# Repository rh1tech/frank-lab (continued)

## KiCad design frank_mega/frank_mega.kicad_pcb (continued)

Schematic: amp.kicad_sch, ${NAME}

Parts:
C36, C41, C46: 1u; C_0805_2012Metric
C37, C38, C39, C43, C44: 10u; C_0805_2012Metric
C40, C45: 100n; C_0805_2012Metric
C42: 10u; CP_Radial_D4.0mm_P1.50mm
C47: 100u; C_Radial_D6.3mm_P2.50mm
R101, R102, R103, R104, R105, R106, R107, R108, R109, R112, R116: 10K; R_0805_2012Metric
R110, R111: 47K; R_0805_2012Metric
R113: 100R; R_0805_2012Metric
R114, R115: 20K; R_0805_2012Metric
U19: PAM8403D; SOP-16_P1.27mm; Mouser Part Number 700-MAX232CSE
U20: LM358; SO-8

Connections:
/Audio Multiplexer/AMP_IN_L: C37.1, R102.1; also elsewhere on the board
/Audio Multiplexer/AMP_IN_R: C38.1, R104.1; also elsewhere on the board
/Audio/AMP_OUTL: C43.2, R114.2; also elsewhere on the board
/Audio/AMP_OUTR: C44.2, R115.2; also elsewhere on the board
/Audio/AMP_PAM_OUTL_M: U19.3 (-OUTL); also elsewhere on the board
/Audio/AMP_PAM_OUTL_P: U19.1 (+OUT_L); also elsewhere on the board
/Audio/AMP_PAM_OUTR_M: U19.14 (-OUT_R); also elsewhere on the board
/Audio/AMP_PAM_OUTR_P: U19.16 (+OUT_R); also elsewhere on the board
/MONO_L: C36.1, R101.1, R102.2; also elsewhere on the board
/MONO_R: C41.1, R103.1, R104.2; also elsewhere on the board
/SHND: R116.2, U19.12 (SHND); also elsewhere on the board
GND: C39.1, C40.2, C42.2, C45.1, C46.2, C47.2, R101.2, R103.2, R106.1, R114.1, R115.1, U19.2 (PGND), U19.11 (GND), U19.15 (PGND), U20.4 (V-); also elsewhere on the board
unnamed: C36.2, R107.2
unnamed: C37.2, R108.2
unnamed: C38.2, R109.2
unnamed: C41.2, R112.2
unnamed: C43.1, R110.1, U20.7
unnamed: C44.1, R111.1, U20.1
unnamed: R107.1, U19.7 (INL)
unnamed: R112.1, U19.10 (INR)
unnamed: C40.1, U19.8 (VREF)
unnamed: C39.2, R105.1, R106.2, U20.3 (+), U20.5 (+)
unnamed: R109.1, R111.2, U20.2 (-)
unnamed: R108.1, R110.2, U20.6 (-)
unnamed: C42.1, C45.2, R105.2, R113.2, U20.8 (V+)
VBUS: C46.1, C47.1, R113.1, R116.1, U19.4 (PVDD), U19.5 (MUTE), U19.6 (VDD), U19.13 (PVDD); also elsewhere on the board

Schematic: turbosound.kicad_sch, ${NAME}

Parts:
C15, C16: 22p; C_0805_2012Metric
C17, C19: 100u; C_Radial_D6.3mm_P2.50mm
C18, C20, C21, C22: 100n; C_0805_2012Metric
D2, D3: 1N4148; D_SOD-323
LD2, LD3: Orange; LED_0805
Q1: BC850; SOT-23
R21, R23, R28, R36, R37: 1K; R_0805_2012Metric
R22: 100K; R_0805_2012Metric
R24, R25, R38, R39: 4.7K; R_0805_2012Metric
R26, R27, R40, R41: 2K; R_0805_2012Metric
R29, R30, R31, R32, R33, R34, R35, R44, R46, R49, R51, R53, R56, R58: 10K; R_0805_2012Metric
R42, R43, R45, R48, R50, R52, R54, R57, R59: 20K; R_0805_2012Metric
R47, R55: 120R; R_0805_2012Metric
S8: TS Reset; Button_SMD_3x4x2mm; Mouser Part Number 611-KMR221G-LFS
U5, U7: JFC95101; DIP-40_W15.24mm_Socket
U6: 74HC74; SOIC-14_P1.27mm
U8, U9: 74HC595; SOP-16_P1.27mm
X1: 3.58 MHz; Crystal_HC49-S

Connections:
/Audio/TS/A1: R26.2, U5.4 (B)
/Audio/TS/A2: R40.2, U7.4 (B)
/Audio/TS/B1: R24.2, R25.2, U5.3 (A)
/Audio/TS/B2: R38.2, R39.2, U7.3 (A)
/Audio/TS/BEEP: R32.2, R33.2, U9.4 (QE)
/Audio/TS/C1: R27.2, U5.38 (C)
/Audio/TS/C2: R41.2, U7.38 (C)
/Audio/TS/CLK_1.75M: U5.22 (CLOCK), U6.5 (Q), U7.22 (CLOCK)
/Audio/TS/COVOX_OUT: R30.2, R31.2, R58.2, R59.1
/Audio/TS/DA0: U5.37 (DA0), U7.37 (DA0), U8.15 (QA)
/Audio/TS/DA1: U5.36 (DA1), U7.36 (DA1), U8.1 (QB)
/Audio/TS/DA2: U5.35 (DA2), U7.35 (DA2), U8.2 (QC)
/Audio/TS/DA3: U5.34 (DA3), U7.34 (DA3), U8.3 (QD)
/Audio/TS/DA4: U5.33 (DA4), U7.33 (DA4), U8.4 (QE)
/Audio/TS/DA5: U5.32 (DA5), U7.32 (DA5), U8.5 (QF)
/Audio/TS/DA6: U5.31 (DA6), U7.31 (DA6), U8.6 (QG)
/Audio/TS/DA7: U5.30 (DA7), U7.30 (DA7), U8.7 (QH)
/Audio/TS/DAC0: R43.2, U7.13 (IOB0)
/Audio/TS/DAC1: R45.2, U7.12 (IOB1)
/Audio/TS/DAC2: R48.2, U7.11 (IOB2)
/Audio/TS/DAC3: R50.2, U7.10 (IOB3)
/Audio/TS/DAC4: R52.2, U7.9 (IOB4)
/Audio/TS/DAC5: R54.2, U7.8 (IOB5)
/Audio/TS/DAC6: R57.2, U7.7 (IOB6)
/Audio/TS/DAC7: R59.2, U7.6 (IOB7)
/Audio/TS/L_IN: R25.1, R26.1, R31.1, R33.1, R35.1, R39.1, R40.1, R47.1; also elsewhere on the board
/Audio/TS/R_IN: R24.1, R27.1, R30.1, R32.1, R34.1, R38.1, R41.1, R55.1; also elsewhere on the board
/Audio/TS/SAVE: R34.2, R35.2, U9.5 (QF)
/Audio/TS/YM_BC1: U5.29 (BC1), U7.29 (BC1), U9.15 (QA)
/Audio/TS/YM_BDIR: U5.27 (BDIR), U7.27 (BDIR), U9.1 (QB)
/Audio/TS/YM_CS1: LD2.2 (A), U5.25 (A8), U9.2 (QC)
/Audio/TS/YM_CS2: LD3.2 (A), U7.25 (A8), U9.3 (QD)
/Audio/TS/YM_RST: D2.2 (A), D3.2 (A), R29.1, U5.23 (~RESET), U7.23 (~RESET)
/Audio/TS/YM_SEL1: R21.2, U5.26 (~SEL)
/Audio/TS/YM_SEL2: R28.2, U7.26 (~SEL)
/PGPIO9: U8.12 (RCLK), U9.12 (RCLK); also elsewhere on the board
/PGPIO10: U8.11 (SRCLK), U9.11 (SRCLK); also elsewhere on the board
/PGPIO11: U8.14 (SER); also elsewhere on the board
GND: C15.1, C16.1, C17.2, C18.2, C19.2, C20.2, C21.2, C22.2, Q1.2 (E), R36.1, R37.1, R42.1, R47.2, R55.2, S8.2, S8.4, U5.1 (VSS), U5.24 (~A9), U6.7 (GND), U7.1 (VSS), U7.24 (~A9), U8.8 (GND), U8.13 (~OE), U9.8 (GND), U9.13 (~OE); also elsewhere on the board
unnamed: D2.1 (K), S8.1, S8.3
unnamed: D3.1 (K), U9.6 (QG)
unnamed: LD2.1 (K), R36.2
unnamed: LD3.1 (K), R37.2
unnamed: C15.2, Q1.1 (B), R22.1, X1.1
unnamed: C16.2, Q1.3 (C), R22.2, R23.1, U6.3 (C), X1.2
unnamed: R42.2, R43.1, R44.1
unnamed: R44.2, R45.1, R46.1
unnamed: R46.2, R48.1, R49.1
unnamed: R49.2, R50.1, R51.1
unnamed: R51.2, R52.1, R53.1
unnamed: R53.2, R54.1, R56.1
unnamed: R56.2, R57.1, R58.1
unnamed: U6.2 (D), U6.6 (~Q)
unnamed: U8.9 (QH'), U9.14 (SER)
VBUS: C17.1, C18.1, C19.1, C20.1, C21.1, C22.1, R21.1, R23.2, R28.1, R29.2, U5.28 (BC2), U5.40 (VCC), U6.1 (~R), U6.4 (~S), U6.14 (VCC), U7.28 (BC2), U7.40 (VCC), U8.10 (~SRCLR), U8.16 (VCC), U9.10 (~SRCLR), U9.16 (VCC); also elsewhere on the board

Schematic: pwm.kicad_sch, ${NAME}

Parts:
C31, C32: 47n; C_0805_2012Metric
R90, R92: 10K; R_0805_2012Metric
R91, R93, R94, R95: 2K; R_0805_2012Metric
R96, R97: 1K; R_0805_2012Metric

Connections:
/Audio Multiplexer/PWM_OUT_L: R92.2, R93.1; also elsewhere on the board
/Audio Multiplexer/PWM_OUT_R: R90.2, R91.1; also elsewhere on the board
/PGPIO9: R94.1, R95.1; also elsewhere on the board
/PGPIO10: R97.2; also elsewhere on the board
/PGPIO11: R96.2; also elsewhere on the board
GND: C31.2, C32.2, R91.2, R93.2; also elsewhere on the board
unnamed: C31.1, R90.1, R94.2, R97.1
unnamed: C32.1, R92.1, R95.2, R96.1

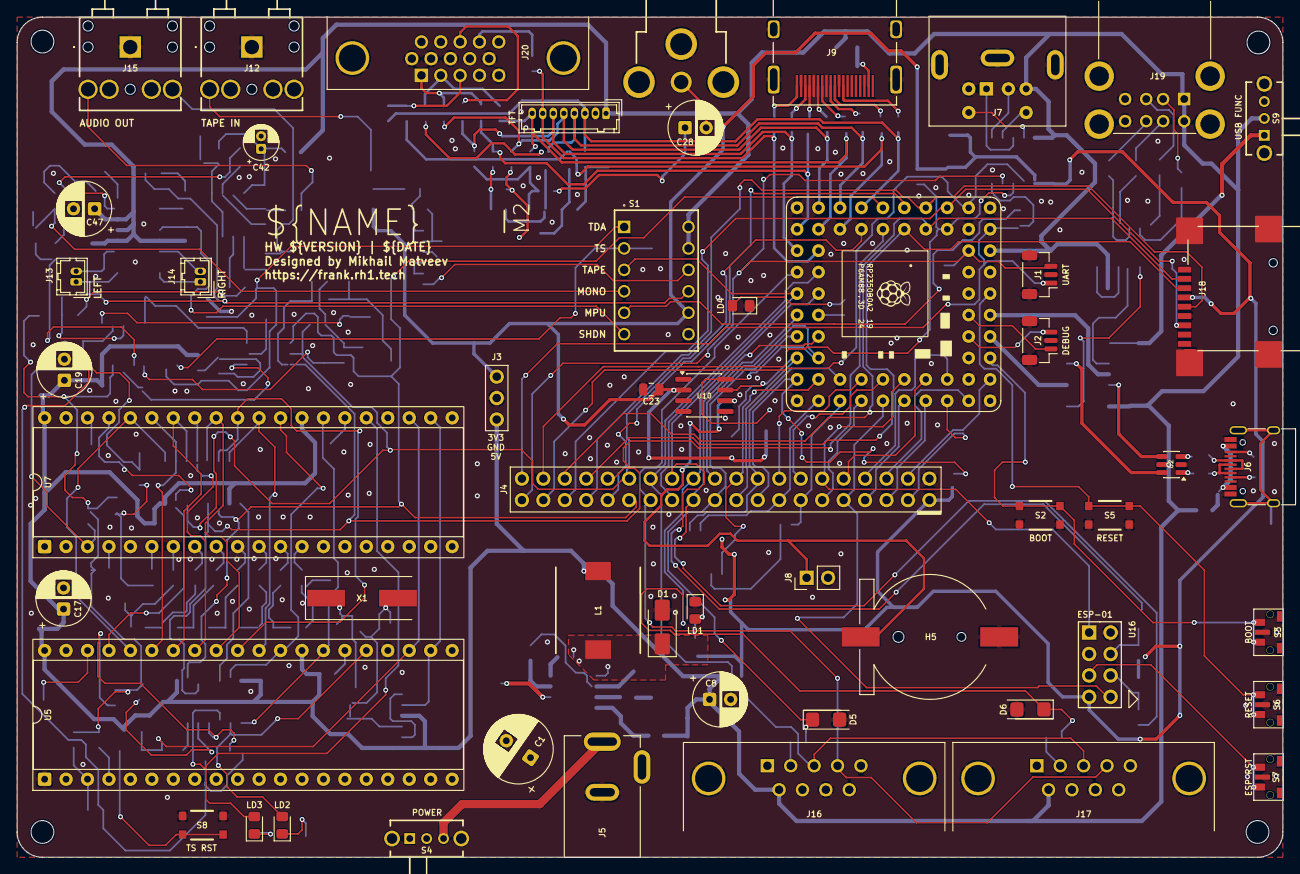
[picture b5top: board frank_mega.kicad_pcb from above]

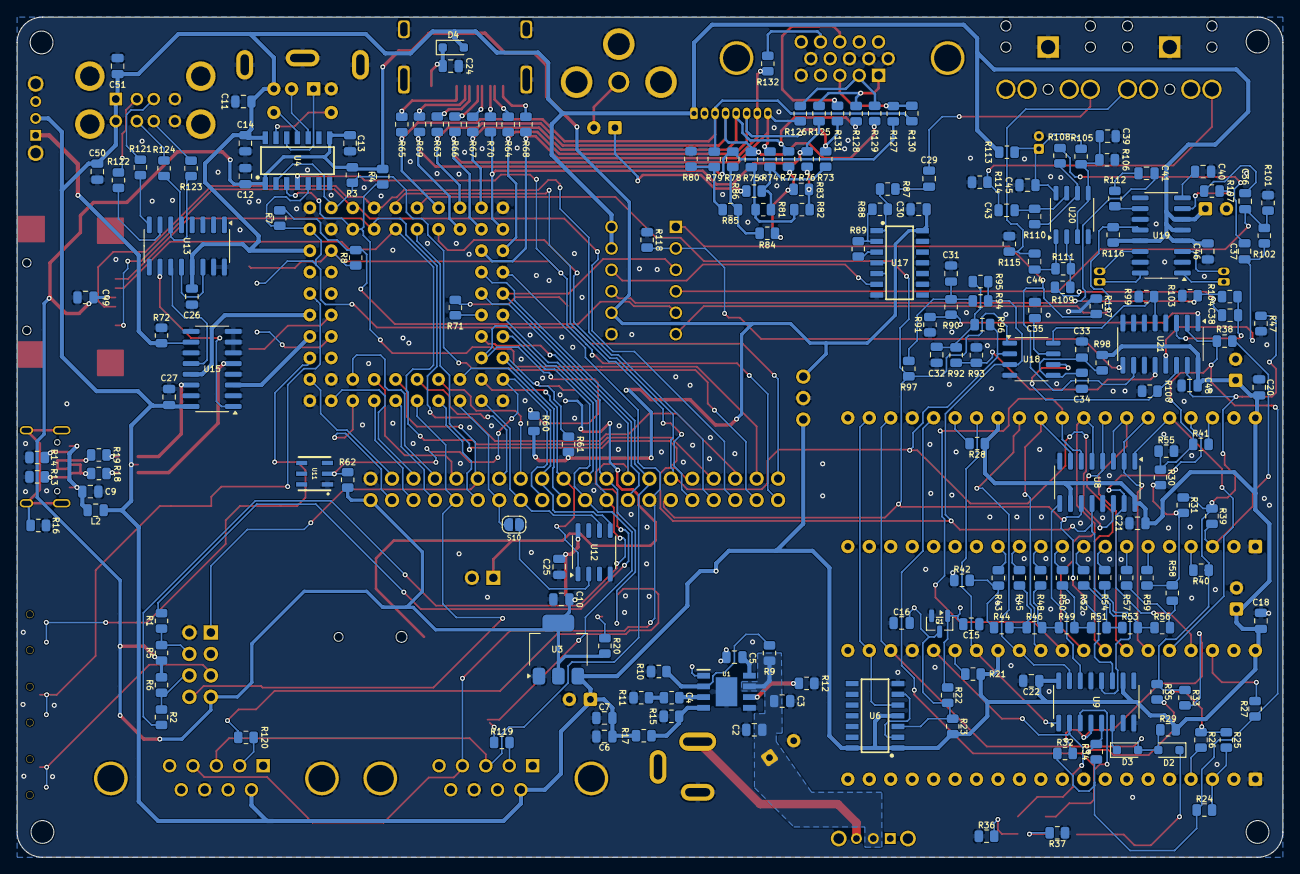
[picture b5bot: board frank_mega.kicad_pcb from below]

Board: 2 copper layers, 149.9 x 99.5 mm, 253 parts (196 on the bottom side), 214 nets.

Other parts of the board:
S7: ESP Reset; Button_SMD_TS1234VW

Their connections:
/ESP Reset/RST: S7.1; also elsewhere on the board
GND: S7.2, S7.3 (GND); also elsewhere on the board

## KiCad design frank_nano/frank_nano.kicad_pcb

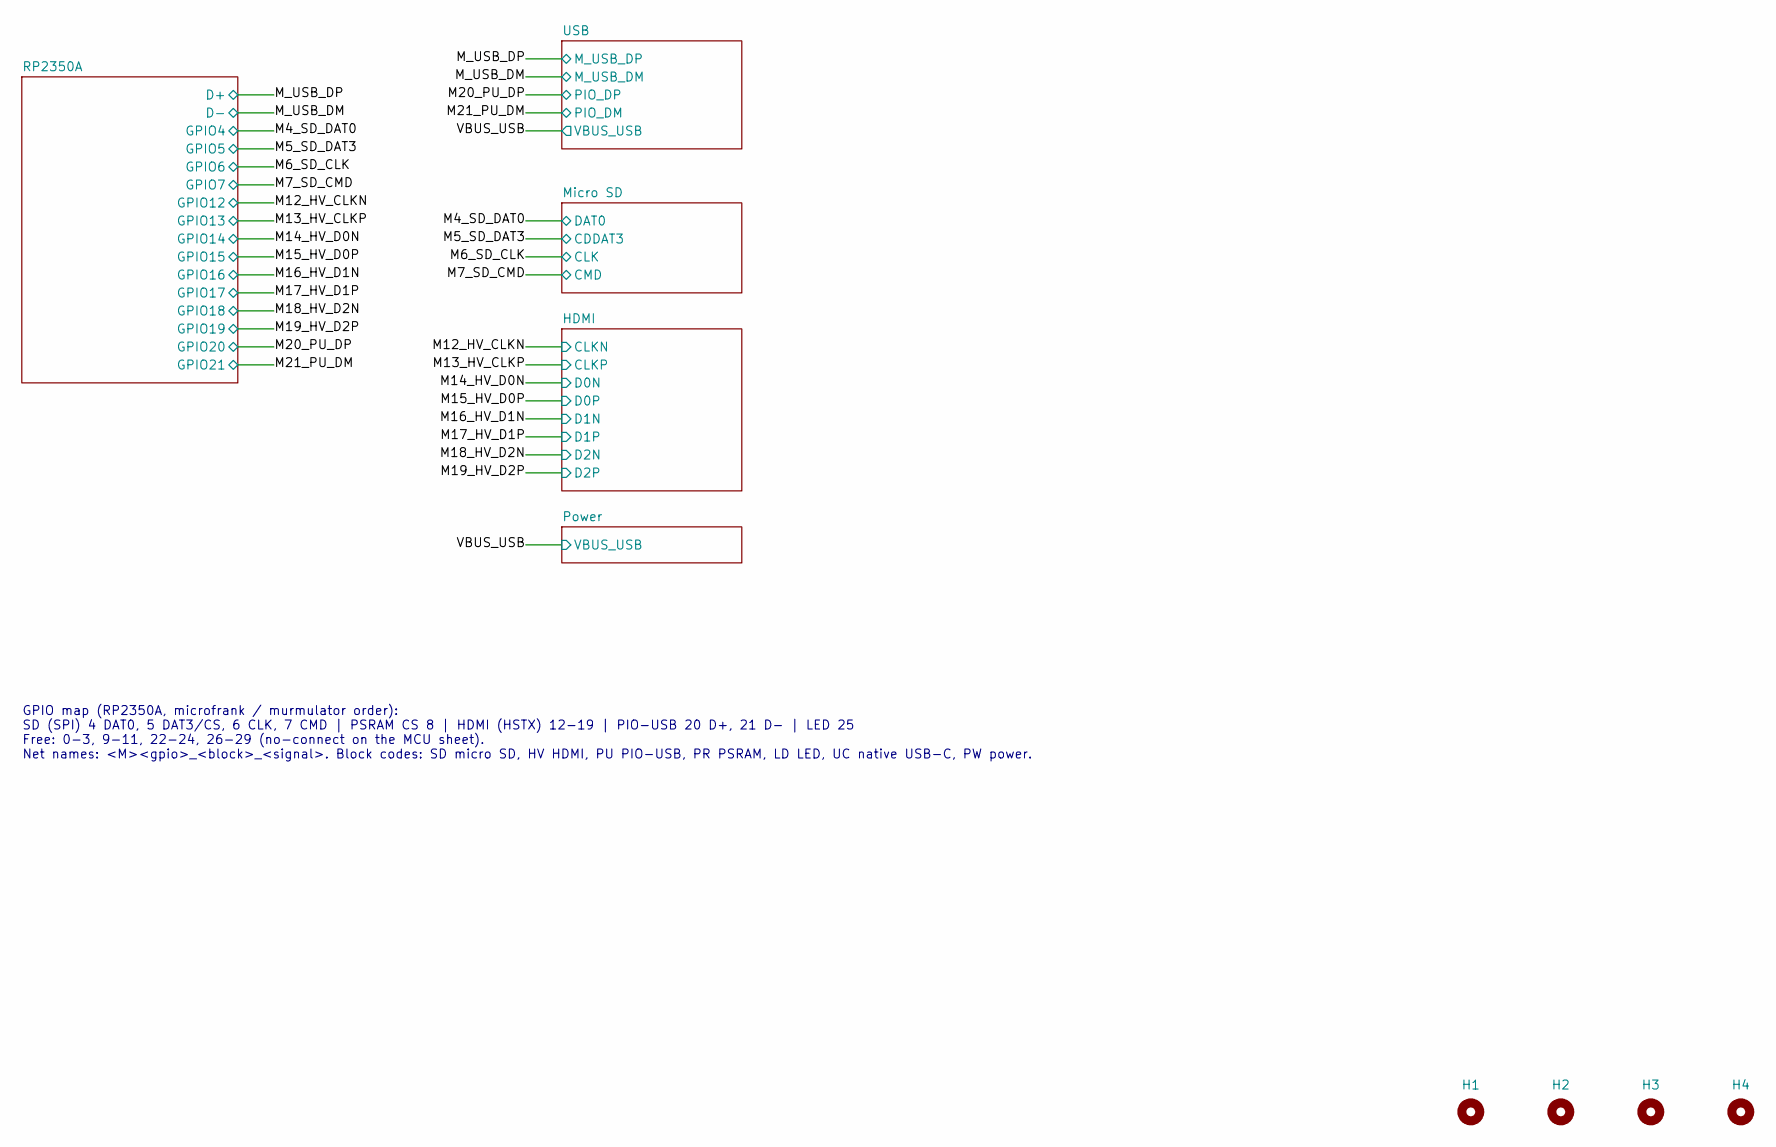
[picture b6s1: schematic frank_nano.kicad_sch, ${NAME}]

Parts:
H1, H2, H3, H4: Mounting Hole (3.0mm); MountingHole_3.0mm

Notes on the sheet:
GPIO map (RP2350A, microfrank / murmulator order): SD (SPI) 4 DAT0, 5 DAT3/CS, 6 CLK, 7 CMD | PSRAM CS 8 | HDMI (HSTX) 12-19 | PIO-USB 20 D+, 21 D- | LED 25 Free: 0-3, 9-11, 22-24, 26-29 (no-connect on the MCU sheet). Net names: <M><gpio>_<block>_<signal>. Block codes: SD micro SD, HV HDMI, PU PIO-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

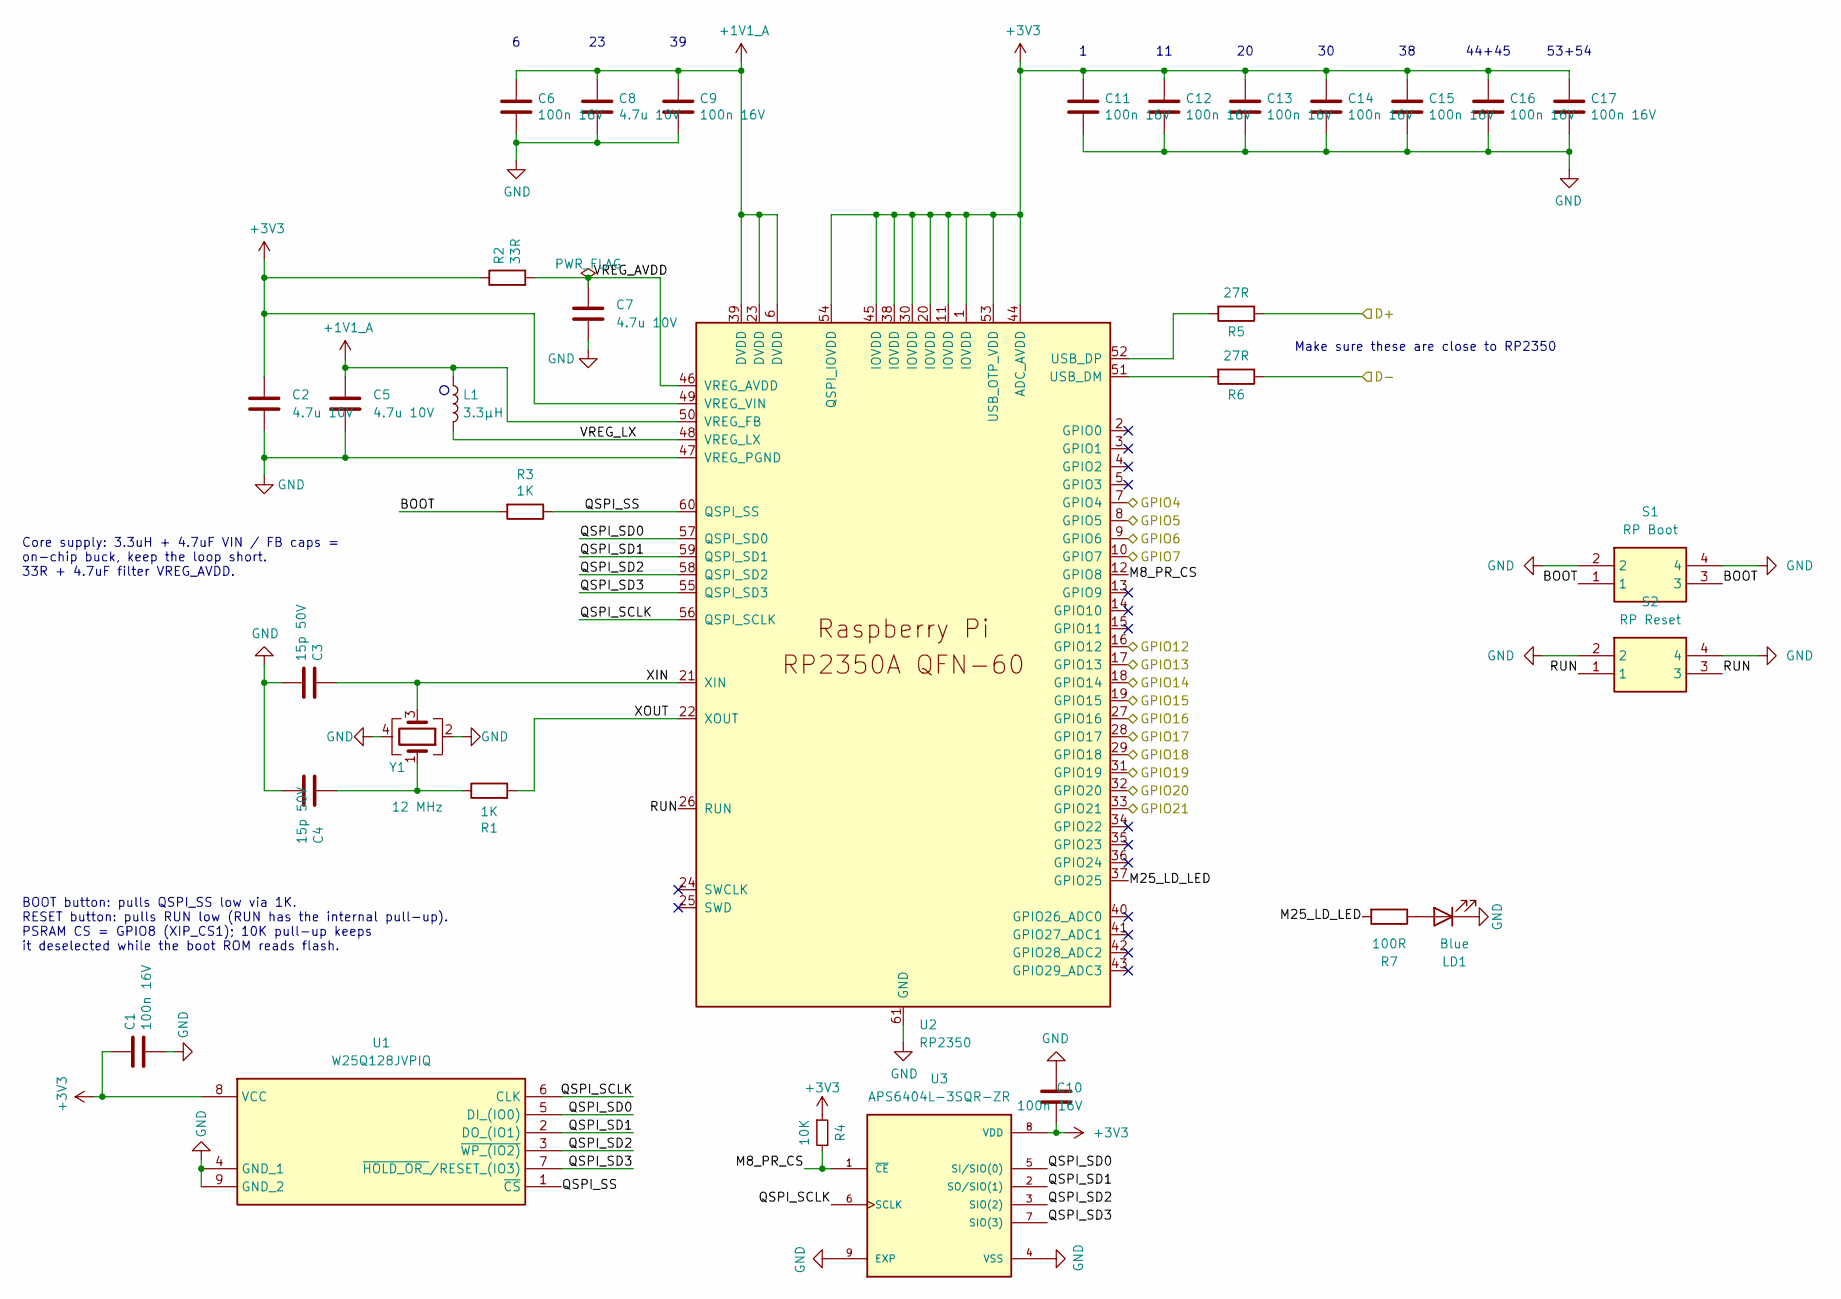
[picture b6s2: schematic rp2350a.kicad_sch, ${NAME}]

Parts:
C1, C6, C9, C10: 100n 16V; C_0402_1005Metric_small_pads_Via; LCSC C1525
C2, C5, C7: 4.7u 10V; C_0402_1005Metric_small_pads; LCSC C23733
C3, C4: 15p 50V; C_0402_1005Metric_small_pads; LCSC C1548
C8: 4.7u 10V; C_0402_1005Metric_small_pads_Via_GND; LCSC C23733
C11, C12, C13, C14, C15, C16, C17: 100n 16V; C_0402_1005Metric_small_pads_Via_GND; LCSC C1525
L1: 3.3µH; L_AOTA-B201610_2.0x1.6mm; LCSC C42411119
LD1: Blue; LED_0603_1608Metric; LCSC C965807
R1, R3: 1K; R_0402_1005Metric; LCSC C11702
R2: 33R; R_0402_1005Metric_small_pads_Via; LCSC C25105
R4: 10K; R_0402_1005Metric_small_pads_Via; LCSC C25744
R5, R6: 27R; R_0402_1005Metric; LCSC C25100
R7: 100R; R_0402_1005Metric; LCSC C25076
S1: RP Boot; Button_SMD_3x4x2mm; LCSC C72443
S2: RP Reset; Button_SMD_3x4x2mm; LCSC C72443
U1: W25Q128JVPIQ; WSON-8-1EP_6x5mm_P1.27mm_EP3.45x4.35mm; Mouser Part Number 454-W25Q128JVPIQ; LCSC C190862
U2: RP2350; QFN-60-1EP_7x7mm_P0.4mm_EP3.4x3.4mm; LCSC C42411118
U3: APS6404L-3SQR-ZR; PSON50P200X300X50-9N; PARTREV 2.3; LCSC C3040877
Y1: 12 MHz; Crystal_SMD_3225-4Pin_3.2x2.5mm; LCSC C20625731

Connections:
+1V1_A: C5.1, C6.1, C8.1, C9.1, L1.1, U2.6 (DVDD), U2.23 (DVDD), U2.39 (DVDD), U2.50 (VREG_FB); also elsewhere on the board
+3V3: C1.1, C2.1, C10.1, C11.1, C12.1, C13.1, C14.1, C15.1, C16.1, C17.1, R2.1, R4.1, U1.8 (VCC), U2.1 (IOVDD), U2.11 (IOVDD), U2.20 (IOVDD), U2.30 (IOVDD), U2.38 (IOVDD), U2.44 (ADC_AVDD), U2.45 (IOVDD), U2.49 (VREG_VIN), U2.53 (USB_OTP_VDD), U2.54 (QSPI_IOVDD), U3.8 (VDD); also elsewhere on the board
/M4_SD_DAT0: U2.7 (GPIO4); also elsewhere on the board
/M5_SD_DAT3: U2.8 (GPIO5); also elsewhere on the board
/M6_SD_CLK: U2.9 (GPIO6); also elsewhere on the board
/M7_SD_CMD: U2.10 (GPIO7); also elsewhere on the board
/M12_HV_CLKN: U2.16 (GPIO12); also elsewhere on the board
/M13_HV_CLKP: U2.17 (GPIO13); also elsewhere on the board
/M14_HV_D0N: U2.18 (GPIO14); also elsewhere on the board
/M15_HV_D0P: U2.19 (GPIO15); also elsewhere on the board
/M16_HV_D1N: U2.27 (GPIO16); also elsewhere on the board
/M17_HV_D1P: U2.28 (GPIO17); also elsewhere on the board
/M18_HV_D2N: U2.29 (GPIO18); also elsewhere on the board
/M19_HV_D2P: U2.31 (GPIO19); also elsewhere on the board
/M20_PU_DP: U2.32 (GPIO20); also elsewhere on the board
/M21_PU_DM: U2.33 (GPIO21); also elsewhere on the board
/M_USB_DM: R6.1; also elsewhere on the board
/M_USB_DP: R5.1; also elsewhere on the board
/RP2350A/BOOT: R3.2, S1.1, S1.3
/RP2350A/M8_PR_CS: R4.2, U2.12 (GPIO8), U3.1 (~CE)
/RP2350A/M25_LD_LED: R7.2, U2.37 (GPIO25)
/RP2350A/QSPI_SCLK: U1.6 (CLK), U2.56 (QSPI_SCLK), U3.6 (SCLK)
/RP2350A/QSPI_SD0: U1.5 (DI_(IO0)), U2.57 (QSPI_SD0), U3.5 (SI/SIO(0))
/RP2350A/QSPI_SD1: U1.2 (DO_(IO1)), U2.59 (QSPI_SD1), U3.2 (SO/SIO(1))
/RP2350A/QSPI_SD2: U1.3 (~WP_(IO2)), U2.58 (QSPI_SD2), U3.3 (SIO(2))
/RP2350A/QSPI_SD3: U1.7 (~HOLD_OR_/RESET_(IO3)), U2.55 (QSPI_SD3), U3.7 (SIO(3))
/RP2350A/QSPI_SS: R3.1, U1.1 (~CS), U2.60 (QSPI_SS)
/RP2350A/RUN: S2.1, S2.3, U2.26 (RUN)
/RP2350A/VREG_AVDD: C7.1, R2.2, U2.46 (VREG_AVDD)
/RP2350A/VREG_LX: L1.2, U2.48 (VREG_LX)
/RP2350A/XIN: C3.1, U2.21 (XIN), Y1.3
/RP2350A/XOUT: R1.2, U2.22 (XOUT)
GND: C1.2, C2.2, C3.2, C4.2, C5.2, C6.2, C7.2, C8.2, C9.2, C10.2, C11.2, C12.2, C13.2, C14.2, C15.2, C16.2, C17.2, LD1.1 (K), S1.2, S1.4, S2.2, S2.4, U1.4 (GND_1), U1.9 (GND_2), U2.47 (VREG_PGND), U2.61 (GND), U3.4 (VSS), U3.9 (EXP), Y1.2, Y1.4; also elsewhere on the board
unnamed: C4.1, R1.1, Y1.1
unnamed: LD1.2 (A), R7.1
unnamed: R6.2, U2.51 (USB_DM)
unnamed: R5.2, U2.52 (USB_DP)

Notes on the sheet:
44+45
Core supply: 3.3uH + 4.7uF VIN / FB caps = on-chip buck, keep the loop short. 33R + 4.7uF filter VREG_AVDD.
Make sure these are close to RP2350
BOOT button: pulls QSPI_SS low via 1K. RESET button: pulls RUN low (RUN has the internal pull-up). PSRAM CS = GPIO8 (XIP_CS1); 10K pull-up keeps it deselected while the boot ROM reads flash.
53+54

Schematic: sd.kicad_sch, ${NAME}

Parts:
C18: 100n 16V; C_0402_1005Metric_small_pads_Via_GND; LCSC C1525
J4: 104031-0811; LCSC C585350

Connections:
+3V3: C18.1, J4.4 (VDD); also elsewhere on the board
/M4_SD_DAT0: J4.7 (DAT0); also elsewhere on the board
/M5_SD_DAT3: J4.2 (DAT3/CD); also elsewhere on the board
/M6_SD_CLK: J4.5 (CLK); also elsewhere on the board
/M7_SD_CMD: J4.3 (CMD); also elsewhere on the board
GND: C18.2, J4.6 (VSS), J4.SH (SHIELD); also elsewhere on the board

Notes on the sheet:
SD card from frank_z0, SPI mode: no external pull-ups (firmware enables the RP2350 internal pull-ups on CS, CMD, DAT0, as on microfrank); DAT1/DAT2 unused; 100n decouples the socket VDD.

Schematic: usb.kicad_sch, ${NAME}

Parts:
J2, J3: KH-TYPE-C-16P; USB_C_Receptacle; LCSC C709357
R8, R9, R10, R11: 5.1K; R_0402_1005Metric_small_pads; LCSC C25905
R12, R13: 22R; R_0402_1005Metric; LCSC C25092
U4, U5: USBLC6-2SC6; SOT-23-6; LCSC C7519

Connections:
/M20_PU_DP: R12.2; also elsewhere on the board
/M21_PU_DM: R13.2; also elsewhere on the board
/M_USB_DM: J2.5 (DN2), J2.7 (DN1), U4.3 (I/O2), U4.4 (I/O2); also elsewhere on the board
/M_USB_DP: J2.6 (DP1), J2.8 (DP2), U4.1 (I/O1), U4.6 (I/O1); also elsewhere on the board
/USB/M20_PU_DP_J: J3.6 (DP1), J3.8 (DP2), R12.1, U5.1 (I/O1), U5.6 (I/O1)
/USB/M21_PU_DM_J: J3.5 (DN2), J3.7 (DN1), R13.1, U5.3 (I/O2), U5.4 (I/O2)
/VBUS_USB: J2.2 (VBUS), J2.11 (VBUS), U4.5 (VBUS); also elsewhere on the board
GND: J2.1 (GND), J2.12 (GND), J2.13 (SHIELD), J3.1 (GND), J3.12 (GND), J3.13 (SHIELD), R8.1, R9.2, R10.1, R11.2, U4.2 (GND), U5.2 (GND); also elsewhere on the board
unnamed: J2.4 (CC1), R8.2
unnamed: J2.10 (CC2), R9.1
unnamed: J3.4 (CC1), R10.2
unnamed: J3.10 (CC2), R11.1
VBUS: J3.2 (VBUS), J3.11 (VBUS), U5.5 (VBUS); also elsewhere on the board

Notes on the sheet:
PIO-USB host port: CC 5.1K, USBLC6-2SC6 ESD, 22R series. GPIO20 = D+, GPIO21 = D-. VBUS comes from the board VBUS rail (5 V to the USB device).
Native USB-C (RP2350 USB device / BOOTSEL, 5 V power in): CC 5.1K = sink, USBLC6-2SC6 ESD at the connector. Series 27R for USB_DP/DM sit at the RP2350 (MCU sheet).

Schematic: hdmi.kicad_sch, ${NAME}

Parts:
J5: HDMI-001 19PCBTP; HDMI_Female; LCSC C138388
RN1, RN2: 270R; R_Array_4x0603; LCSC C1731063

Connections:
/M12_HV_CLKN: RN1.4 (R4.1); also elsewhere on the board
/M13_HV_CLKP: RN1.3 (R3.1); also elsewhere on the board
/M14_HV_D0N: RN1.2 (R2.1); also elsewhere on the board
/M15_HV_D0P: RN1.1 (R1.1); also elsewhere on the board
/M16_HV_D1N: RN2.4 (R4.1); also elsewhere on the board
/M17_HV_D1P: RN2.3 (R3.1); also elsewhere on the board
/M18_HV_D2N: RN2.2 (R2.1); also elsewhere on the board
/M19_HV_D2P: RN2.1 (R1.1); also elsewhere on the board
GND: J5.2 (G_D2), J5.5 (G_D1), J5.8 (G_D0), J5.11 (G_CLK), J5.17 (G_DDC/CEC), J5.20 (SHIELD1), J5.21 (SHIELD2), J5.22 (SHIELD3), J5.23 (SHIELD4); also elsewhere on the board
M_HV_5V: J5.18 (+5V); also elsewhere on the board
unnamed: J5.12 (CLKN), RN1.5 (R4.2)
unnamed: J5.10 (CLKP), RN1.6 (R3.2)
unnamed: J5.9 (D0N), RN1.7 (R2.2)
unnamed: J5.7 (D0P), RN1.8 (R1.2)
unnamed: J5.6 (D1N), RN2.5 (R4.2)
unnamed: J5.4 (D1P), RN2.6 (R3.2)
unnamed: J5.3 (D2N), RN2.7 (R2.2)
unnamed: J5.1 (D2P), RN2.8 (R1.2)

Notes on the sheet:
Full-size HDMI Type A receptacle: BOOMELE HDMI-001 19PCBTP (LCSC C138388), footprint from dino_z80. 270R TMDS series arrays as on FRANK Mini; HPD/DDC/CEC not used. HDMI +5V (pin 18, net M_HV_5V) comes from VBUS_USB through a Schottky (power sheet).

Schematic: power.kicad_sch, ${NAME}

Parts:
C20, C21: 10u 25V; C_0603_1608Metric_small_pads_Via_GND; LCSC C96446
D1, D2: 1N5819WS; D_SOD-323; LCSC C191023
LD2: Green; LED_0603_1608Metric; LCSC C965804
R14: 100R; R_0402_1005Metric_small_pads_Via; LCSC C25076
TP1: VBUS_USB; TestPoint_Pad_D1.0mm
TP2: +1V1_A; TestPoint_Pad_D1.0mm
TP3: +3V3; TestPoint_Pad_D1.0mm
TP4: VBUS; TestPoint_Pad_D1.0mm
TP6: M_HV_5V; TestPoint_Pad_D1.0mm
U6: ME6211C33M5; SOT-23-5; LCSC C82942

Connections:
+1V1_A: TP2.1 (1_1); also elsewhere on the board
+3V3: C21.1, R14.1, TP3.1 (1_1), U6.5 (V_{OUT}); also elsewhere on the board
/VBUS_USB: D1.2 (A), D2.2 (A), TP1.1 (1_1); also elsewhere on the board
GND: C20.2, C21.2, LD2.1 (K), U6.2 (V_{SS}); also elsewhere on the board
M_HV_5V: D1.1 (K), TP6.1 (1_1); also elsewhere on the board
unnamed: LD2.2 (A), R14.2
VBUS: C20.1, D2.1 (K), TP4.1 (1_1), U6.1 (V_{IN}), U6.3 (CE); also elsewhere on the board

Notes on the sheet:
3V3: ME6211C33M5 LDO (as on microfrank), CE tied to VIN. 10u in, 10u out. Load ~150-250 mA: (4.6 V - 3.3 V) x 0.2 A = 0.26 W in SOT-23-5, give it a copper pad. RP2350 makes its own 1V1 (on-chip buck).
5 V in: native USB-C -> VBUS_USB -> Schottky -> VBUS rail (no fuse: 5 V-only USB input). VBUS rail feeds the PIO-USB port VBUS (5 V to the USB device) and the 3V3 LDO; the Schottky stops a supply on the PIO-USB port back-feeding the native port. The second Schottky feeds HDMI +5V (M_HV_5V) from VBU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

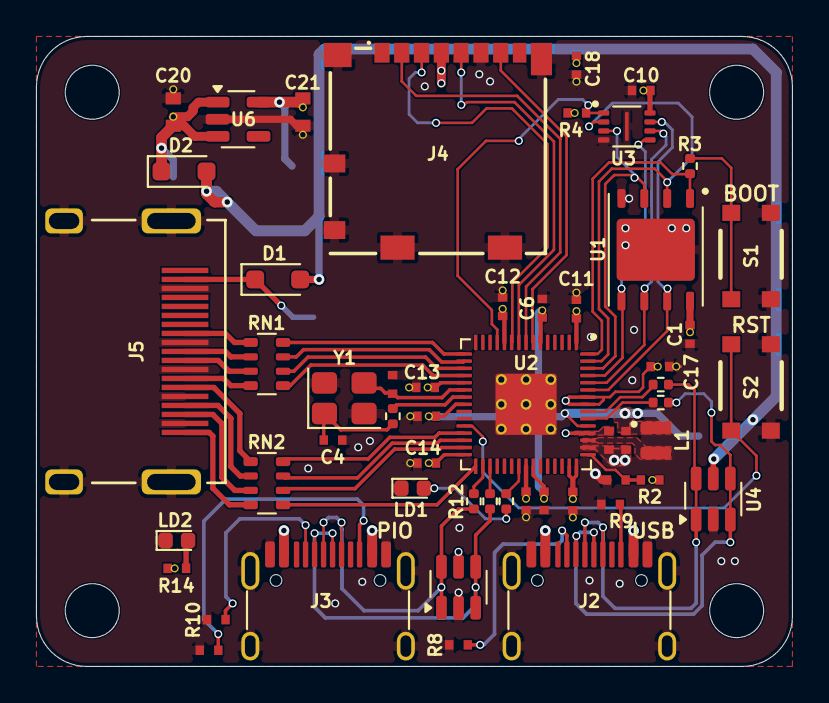
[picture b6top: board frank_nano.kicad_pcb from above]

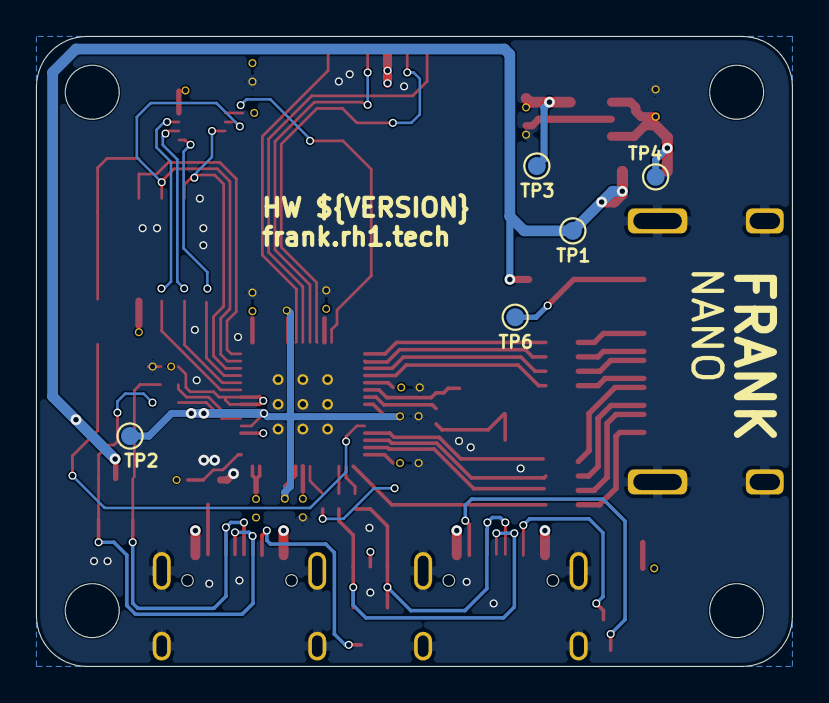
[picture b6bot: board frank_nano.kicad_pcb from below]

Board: 4 copper layers, 42.0 x 35.0 mm, 63 parts (5 on the bottom side), 55 nets.
